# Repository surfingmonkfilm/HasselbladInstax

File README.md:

# HasselbladInstax
For the hosting of project files for the Hasselblad Instaxback created by @SurfingMonkFilm (insta). 

These folders contain all the files needed to recreate the project described on the www.surfingmonk.com site. 

The project is not ready to be followed just yet. This is uploaded for full candidness of our progress so far.

Last Updated 11 Jul 2020.

Any questions should be directed to surfingmonk@protonmail.com in the first instance.

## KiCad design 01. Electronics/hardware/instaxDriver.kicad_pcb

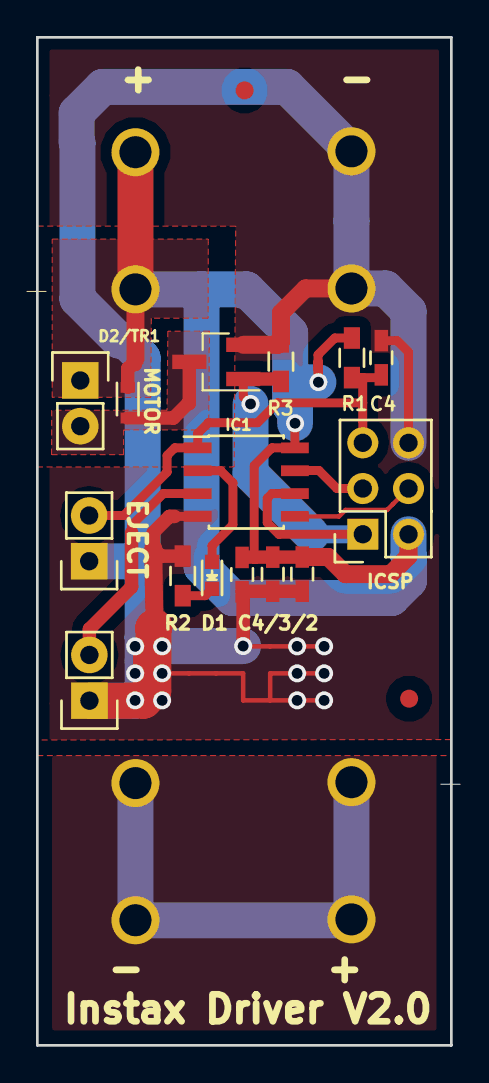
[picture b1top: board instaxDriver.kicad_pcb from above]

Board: 2 copper layers, 23.0 x 56.0 mm, 17 parts (0 on the bottom side), 11 nets.

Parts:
BT1, BT2: BK-82; BAT_BK-82
C1, C4: 100pF; C_0603_HandSoldering
C2: 1uF; C_0603_HandSoldering
C3: 10uF; C_0603_HandSoldering
D1: LED; LED_0603
D2: CD0603-B0240R; D_0603
IC1: ATTINY85-S; SOIC-8_3.9x4.9mm_Pitch1.27mm
P1, P2, P4: CONN_01X02; Socket_Strip_Straight_1x02
P3: CONN_02X03; Socket_Strip_Straight_2x03
R1, R3: 221K; R_0603_HandSoldering
R2: 10K; R_0603_HandSoldering
TR1: BSS806NE; SOT-23_Handsoldering

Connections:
/GND: BT2.S2, C1.2, C2.2, C3.2, C4.2, IC1.4, P1.1, P2.1, P3.6, R2.2, R3.2, TR1.2
/LED_INDICATOR: D1.2, IC1.2
/MISO: IC1.6, P3.1, R3.1, TR1.1
/MOSI: IC1.5, P3.4
/RESET: C4.1, IC1.1, P1.2, P3.5, R1.2
/SCK: IC1.7, P3.3
/SPARE: IC1.3, P2.2
/VCC: BT1.S1, C1.1, C2.1, C3.1, D2.1, IC1.8, P3.2, P4.1, R1.1
unnamed: BT1.S2, BT2.S1
unnamed: D1.1, R2.1
unnamed: D2.2, P4.2, TR1.3

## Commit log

2020-06-21 Create Electronics
2020-07-01 Add electronic design files (hardware and software)
2020-07-01 removed old files
